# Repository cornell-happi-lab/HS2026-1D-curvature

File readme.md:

## 0. Directory Diagram
```
3D_print
    ├── fixture_resin
    ├── MLPdataset
    ├── sensor_case
arduino_code
    ├── multi_test
    ├── single_node
calibration_code
    ├── calibration_data
    ├── calibration_static_multinodes.py
    ├── model_predictNN.py
    ├── plot_static.py
MLPtraining
    ├── runs_strong
    ├── baseline.py
    ├── realtime_prediction_strong_save.py
    ├── sensor_data.csv
    ├── train_strong.py
PCB
    ├── gerbers
    ├── main_board
validation
    ├── daily_objects
    ├── cal_avg_stddev.py
    ├── mygui_sensor_natural.py
    ├── mygui_sensor.py
    ├── validation_data.xlsx
orders.xlsx
```
## 1. Hardware
The tactile sensor is fabricated following a resistive-based design commonly used in tactile sensing research. All required materials — including sensor fabrication supplies, PCB components, cables, and connectors — are listed in [`orders`](orders.xlsx). 

We used KiCad for both the schematic design and PCB layout. The complete board files are available at [`/PCB/main_board`](/PCB/main_board/). The board was manufactured through JLCPCB, and the Gerber files uploaded for fabrication can be found at [`/PCB/gerbers`](/PCB/gerbers/gerber.zip).

An Arduino code [`/arduino_code/multi_test/multi_test.ino`](/arduino_code/multi_test/multi_test.ino) is used to read the sensor data, while a Python script receives the readings through the serial port and performs post-processing.

## 2. Curvature Dataset and Model Training
The sensor can estimate the mean curvature of the surface it is attached to. This is achieved by collecting baseline readings (no force applied) on cylindrical surfaces with different curvatures and training a residual MLP to map these inputs to a single curvature value.

For general 3D surfaces, the model predicts the mean curvature:
```math
\kappa = \tfrac{1}{2}(k_1 + k_2)
```
For cylindrical surfaces, this simplifies to:
```math
\kappa = \tfrac{1}{R} \quad \text{since } k_2 = 0
```

### 2.1 3D Print Fixtures
3D print the cylindrical fixtures with mean curvatures of 0, 10, 20, 30, 40, 50, 60, 70, and 80 m⁻¹. The STEP files are located in [`/3D_print/MLPdataset`](/3D_print/MLPdataset). The radii for each fixture are calculated in [`MLPdataset.xlsx`](/3D_print/MLPdataset/MLPdataset.xlsx).

### 2.2 Collect Baseline Data
After the parts have been printed, attach the sensor onto a fixture and navigate to [`/MLPtraining`](/MLPtraining). Run the following script to collect baseline readings:

```bash
python baseline.py
```
This script collects 100 baseline readings from the sensor and averages them. Save the averaged data to [`/MLPtraining/sensor_data.csv`](/MLPtraining/sensor_data.csv). Then rotate and/or flip the sensor, and repeat this process 10 times for each curvature fixture.

### 2.3 Train the Model
Once all data are collected, run:
```bash
python  train_strong.py
```
This script trains the residual MLP using the collected data and generates a .pt file.

### 2.4 Validate Curvature Prediction
To validate the trained model and test real-time curvature prediction, run
```bash
python realtime_prediction_strong_save.py
```

### 2.5 Pre-Collected Dataset and Model
The dataset used in our paper is available at [`/MLPtraining/sensor_data.csv`](/MLPtraining/sensor_data.csv), and the trained model can be found at [`/MLPtraining/runs_strong/best.pt`](/MLPtraining/runs_strong/best.pt)

## 3. Force Calibration
### 3.1 Hardware Setup
An experimental setup was built for force calibration. The stepper motor and motor controller used in the setup are listed in [`orders.xlsx`](/orders.xlsx). Fixtures with different curvatures were 3D printed using resin, and all corresponding `.stl` files can be found in [`/3D_print/fixture_resin`](/3D_print/fixture_resin/). An [**ATI Nano 17**](https://www.ati-ia.com/products/ft/ft_models.aspx?id=Nano17) force/torque sensor was used as the ground truth reference.  
The 3D-printed mounting case for the FT sensor is available at [`/3D_print/sensor_case`](/3D_print/sensor_case/).

### 3.2 Data Collection
During data collection, the sensor was attached to fixtures with different curvatures. The tip mounted on the ATI Nano 17 force/torque sensor pressed the four central sensing nodes (S5, S6, S9, S10) together as a block, since variations within each block were small and stable. A stepper motor moved incrementally, and at each step, the sensor readings were recorded using the Python script:
```bash
python calibration_static_multinodes.py
```
After data collection, run:
```bash
python plot_static.py
```
to visualize all recorded data under differnt curvatures.

Finally, execute:
```bash
python model_predictNN.py
```
to generate the curvature-aware calibration model. The model is constrained to ensure that all predicted forces are non-negative.

## 4. Validation
We embedded the sensor into five daily objects and developed a GUI to collect static sensing data while a person grasped each object.

To run the GUI, execute the code:
```bash
python mygui_sensor.py
```
During testing, the script automatically records data during periods when the human grasping force matches the preset reference force. We tested four reference forces: 2 N, 4 N, 6 N, and 8 N. All collected data are stored in [`/validation/daily_objects`](/validation/daily_objects/).

To validate sensor's reading under human's natural holding force, run:
```bash
python mygui_sensor_natural.py
```
After collecting all data, calculate the average and standard deviation using:
```bash
python cal_avg_stddev.py
```
All our processed results are stored in ['/validation/validation_data.xlsx'](/validation/validation_data.xlsx).

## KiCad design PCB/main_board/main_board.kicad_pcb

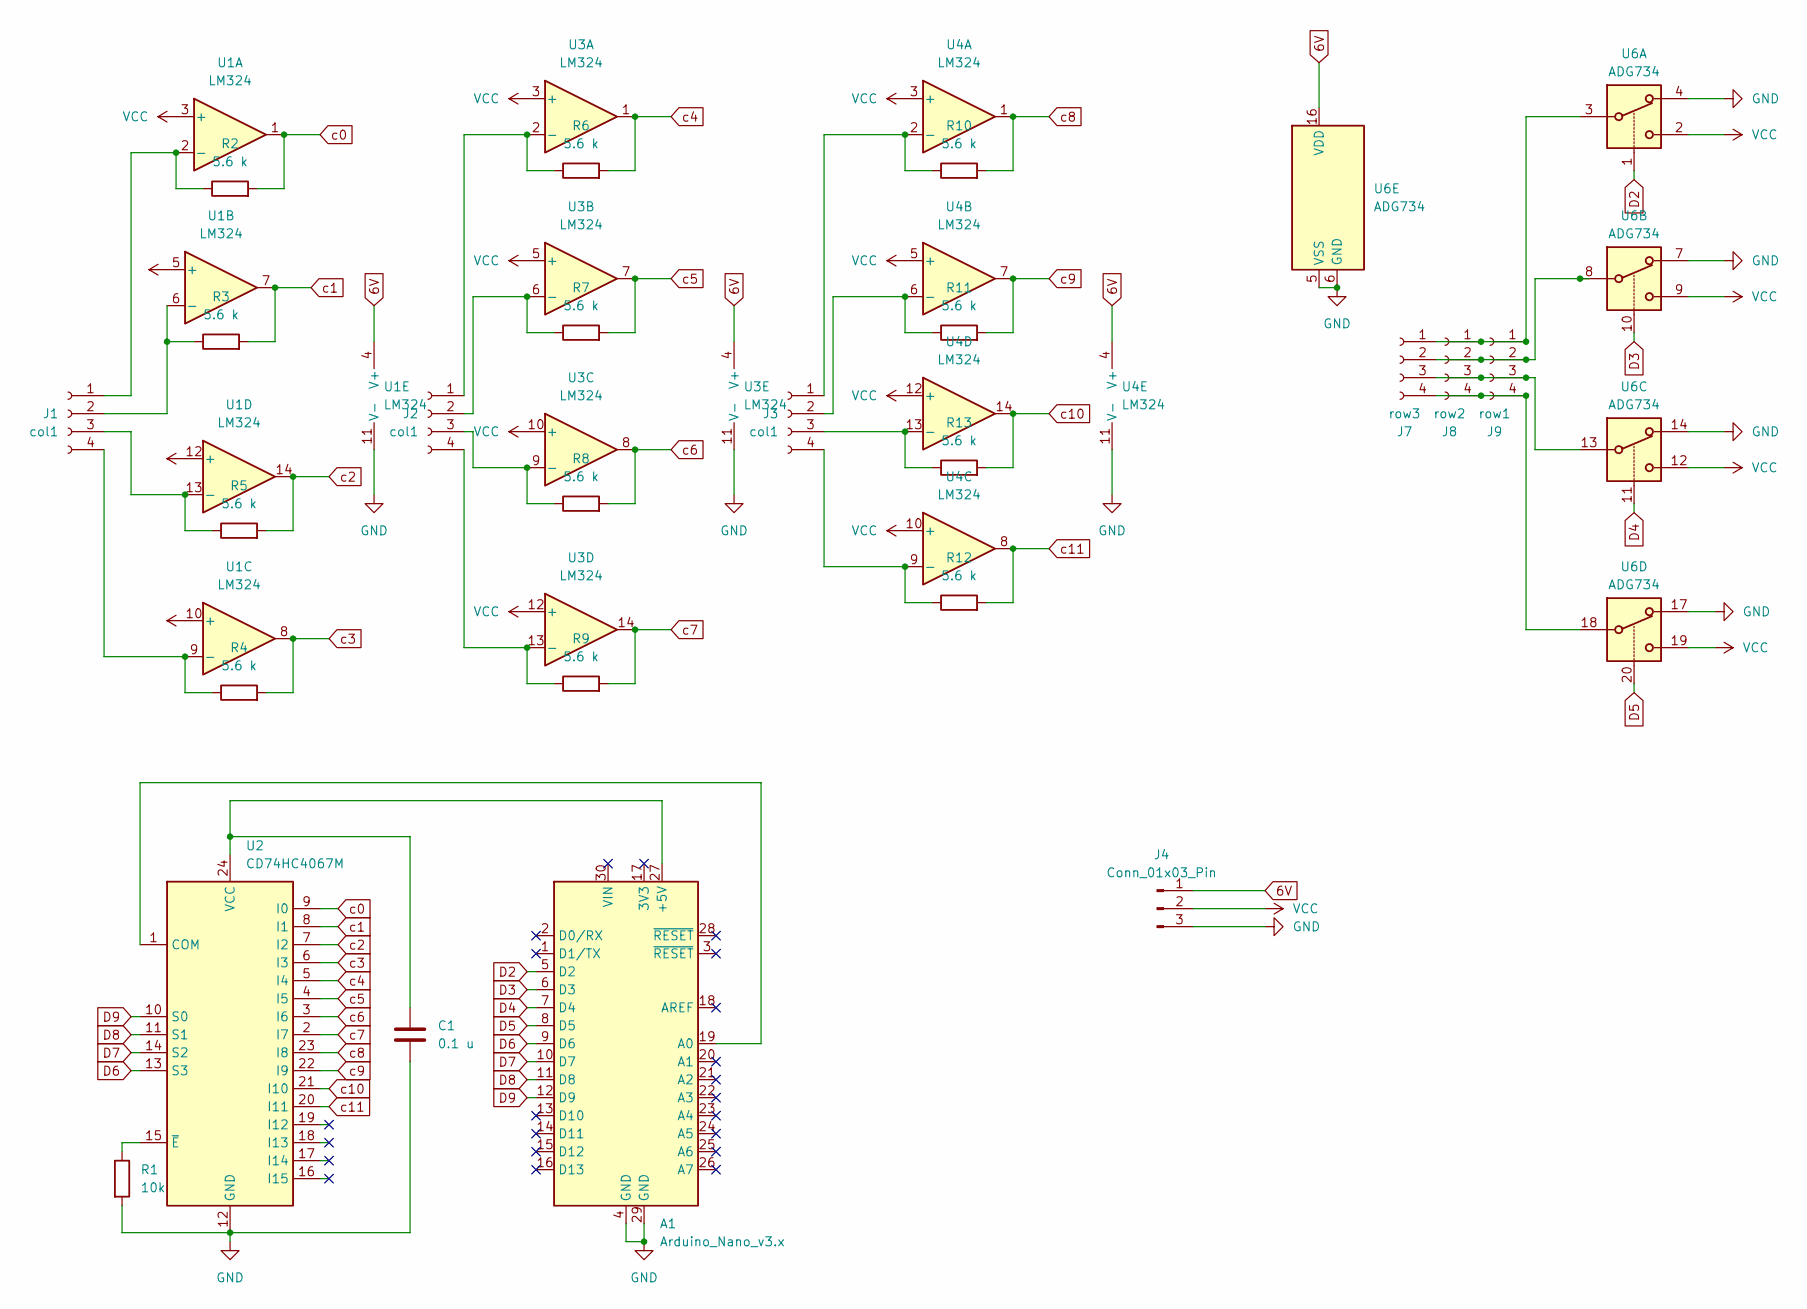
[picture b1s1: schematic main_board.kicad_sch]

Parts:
A1: Arduino_Nano_v3.x; Arduino_Nano
C1: 0.1 u; C_0603_1608Metric_Pad1.08x0.95mm_HandSolder
J1, J2, J3: col1; JST_GH_SM04B-GHS-TB_1x04-1MP_P1.25mm_Horizontal
J4: Conn_01x03_Pin; JST_PH_S3B-PH-SM4-TB_1x03-1MP_P2.00mm_Horizontal
J7: row3; JST_GH_SM04B-GHS-TB_1x04-1MP_P1.25mm_Horizontal
J8: row2; JST_GH_SM04B-GHS-TB_1x04-1MP_P1.25mm_Horizontal
J9: row1; JST_GH_SM04B-GHS-TB_1x04-1MP_P1.25mm_Horizontal
R1: 10k; R_0805_2012Metric_Pad1.20x1.40mm_HandSolder
R2, R3, R4, R5, R6, R7, R8, R9, R10, R11, R12, R13: 5.6 k; R_0805_2012Metric_Pad1.20x1.40mm_HandSolder
U1, U3, U4: LM324; SOIC-14_3.9x8.7mm_P1.27mm
U2: CD74HC4067M; SOIC-24W_7.5x15.4mm_P1.27mm
U6: ADG734; TSSOP-20_4.4x6.5mm_P0.65mm

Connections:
6V: J4.1, U1.4 (V+), U3.4 (V+), U4.4 (V+), U6.16 (VDD)
D2: A1.5 (D2), U6.1
D3: A1.6 (D3), U6.10
D4: A1.7 (D4), U6.11
D5: A1.8 (D5), U6.20
D6: A1.9 (D6), U2.13 (S3)
D7: A1.10 (D7), U2.14 (S2)
D8: A1.11 (D8), U2.11 (S1)
D9: A1.12 (D9), U2.10 (S0)
GND: A1.4 (GND), A1.29 (GND), C1.2, J4.3, R1.2, U1.11 (V-), U2.12 (GND), U3.11 (V-), U4.11 (V-), U6.4, U6.5 (VSS), U6.6 (GND), U6.7, U6.14, U6.17
unnamed: A1.27 (+5V), C1.1, U2.24 (VCC)
unnamed: A1.19 (A0), U2.1 (COM)
unnamed: J1.1, R2.1, U1.2 (-)
unnamed: J1.2, R3.1, U1.6 (-)
unnamed: J1.3, R5.1, U1.13 (-)
unnamed: J1.4, R4.1, U1.9 (-)
unnamed: J2.1, R6.1, U3.2 (-)
unnamed: J2.2, R7.1, U3.6 (-)
unnamed: J2.3, R8.1, U3.9 (-)
unnamed: J2.4, R9.1, U3.13 (-)
unnamed: J3.1, R10.1, U4.2 (-)
unnamed: J3.2, R11.1, U4.6 (-)
unnamed: J3.3, R13.1, U4.13 (-)
unnamed: J3.4, R12.1, U4.9 (-)
unnamed: J7.1, J8.1, J9.1, U6.3
unnamed: J7.2, J8.2, J9.2, U6.8
unnamed: J7.3, J8.3, J9.3, U6.13
unnamed: J7.4, J8.4, J9.4, U6.18
unnamed: R1.1, U2.15 (~E)
VCC: J4.2, U1.3 (+), U1.5 (+), U1.10 (+), U1.12 (+), U3.3 (+), U3.5 (+), U3.10 (+), U3.12 (+), U4.3 (+), U4.5 (+), U4.10 (+), U4.12 (+), U6.2, U6.9, U6.12, U6.19
c0: R2.2, U1.1, U2.9 (I0)
c1: R3.2, U1.7, U2.8 (I1)
c2: R5.2, U1.14, U2.7 (I2)
c3: R4.2, U1.8, U2.6 (I3)
c4: R6.2, U2.5 (I4), U3.1
c5: R7.2, U2.4 (I5), U3.7
c6: R8.2, U2.3 (I6), U3.8
c7: R9.2, U2.2 (I7), U3.14
c8: R10.2, U2.23 (I8), U4.1
c9: R11.2, U2.22 (I9), U4.7
c10: R13.2, U2.21 (I10), U4.14
c11: R12.2, U2.20 (I11), U4.8

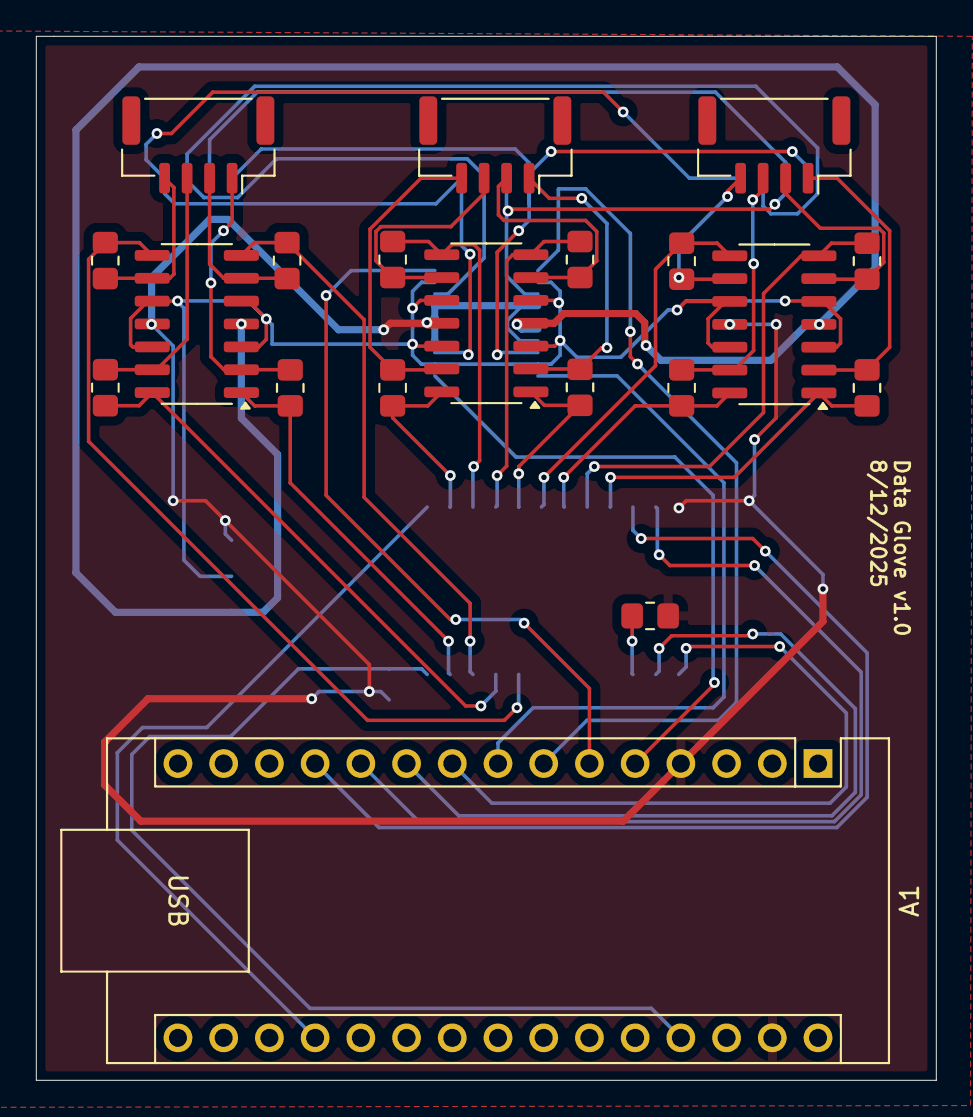
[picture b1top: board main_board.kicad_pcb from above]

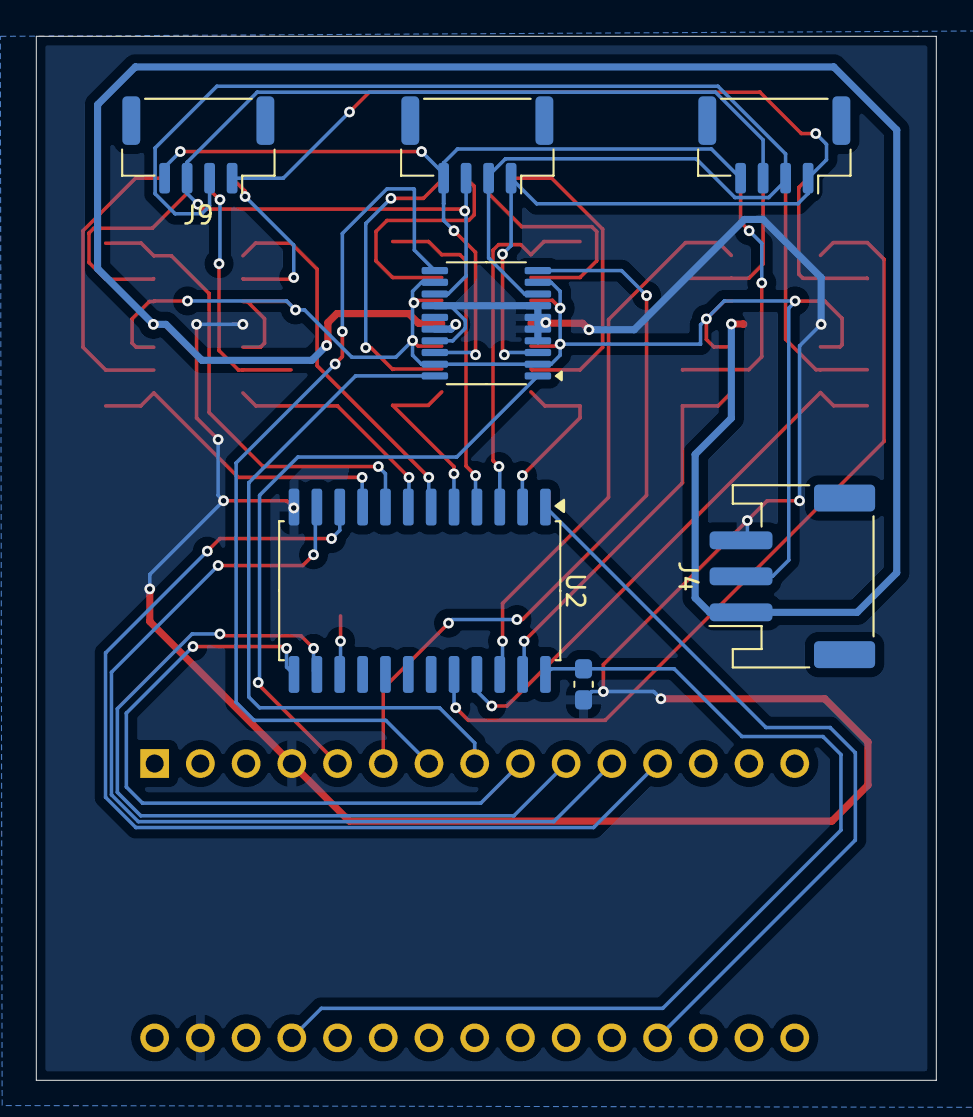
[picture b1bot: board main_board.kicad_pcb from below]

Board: 2 copper layers, 50.0 x 58.0 mm, 27 parts (7 on the bottom side), 42 nets.

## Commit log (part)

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2025-06-06 data collection
2025-06-06 initial commit again
2025-06-10 calibration #2
2025-06-10 accuracy plot added
2025-06-17 Multi-nodes cal files
2025-06-24 finished calibration
2025-07-21 add curvature cal
2025-08-06 calibration finished
2025-09-18 fixed curvature prediction
2025-10-15 final version
2025-11-03 fixed the link
2025-11-03 fixed the math expression
2025-11-03 add diagram
